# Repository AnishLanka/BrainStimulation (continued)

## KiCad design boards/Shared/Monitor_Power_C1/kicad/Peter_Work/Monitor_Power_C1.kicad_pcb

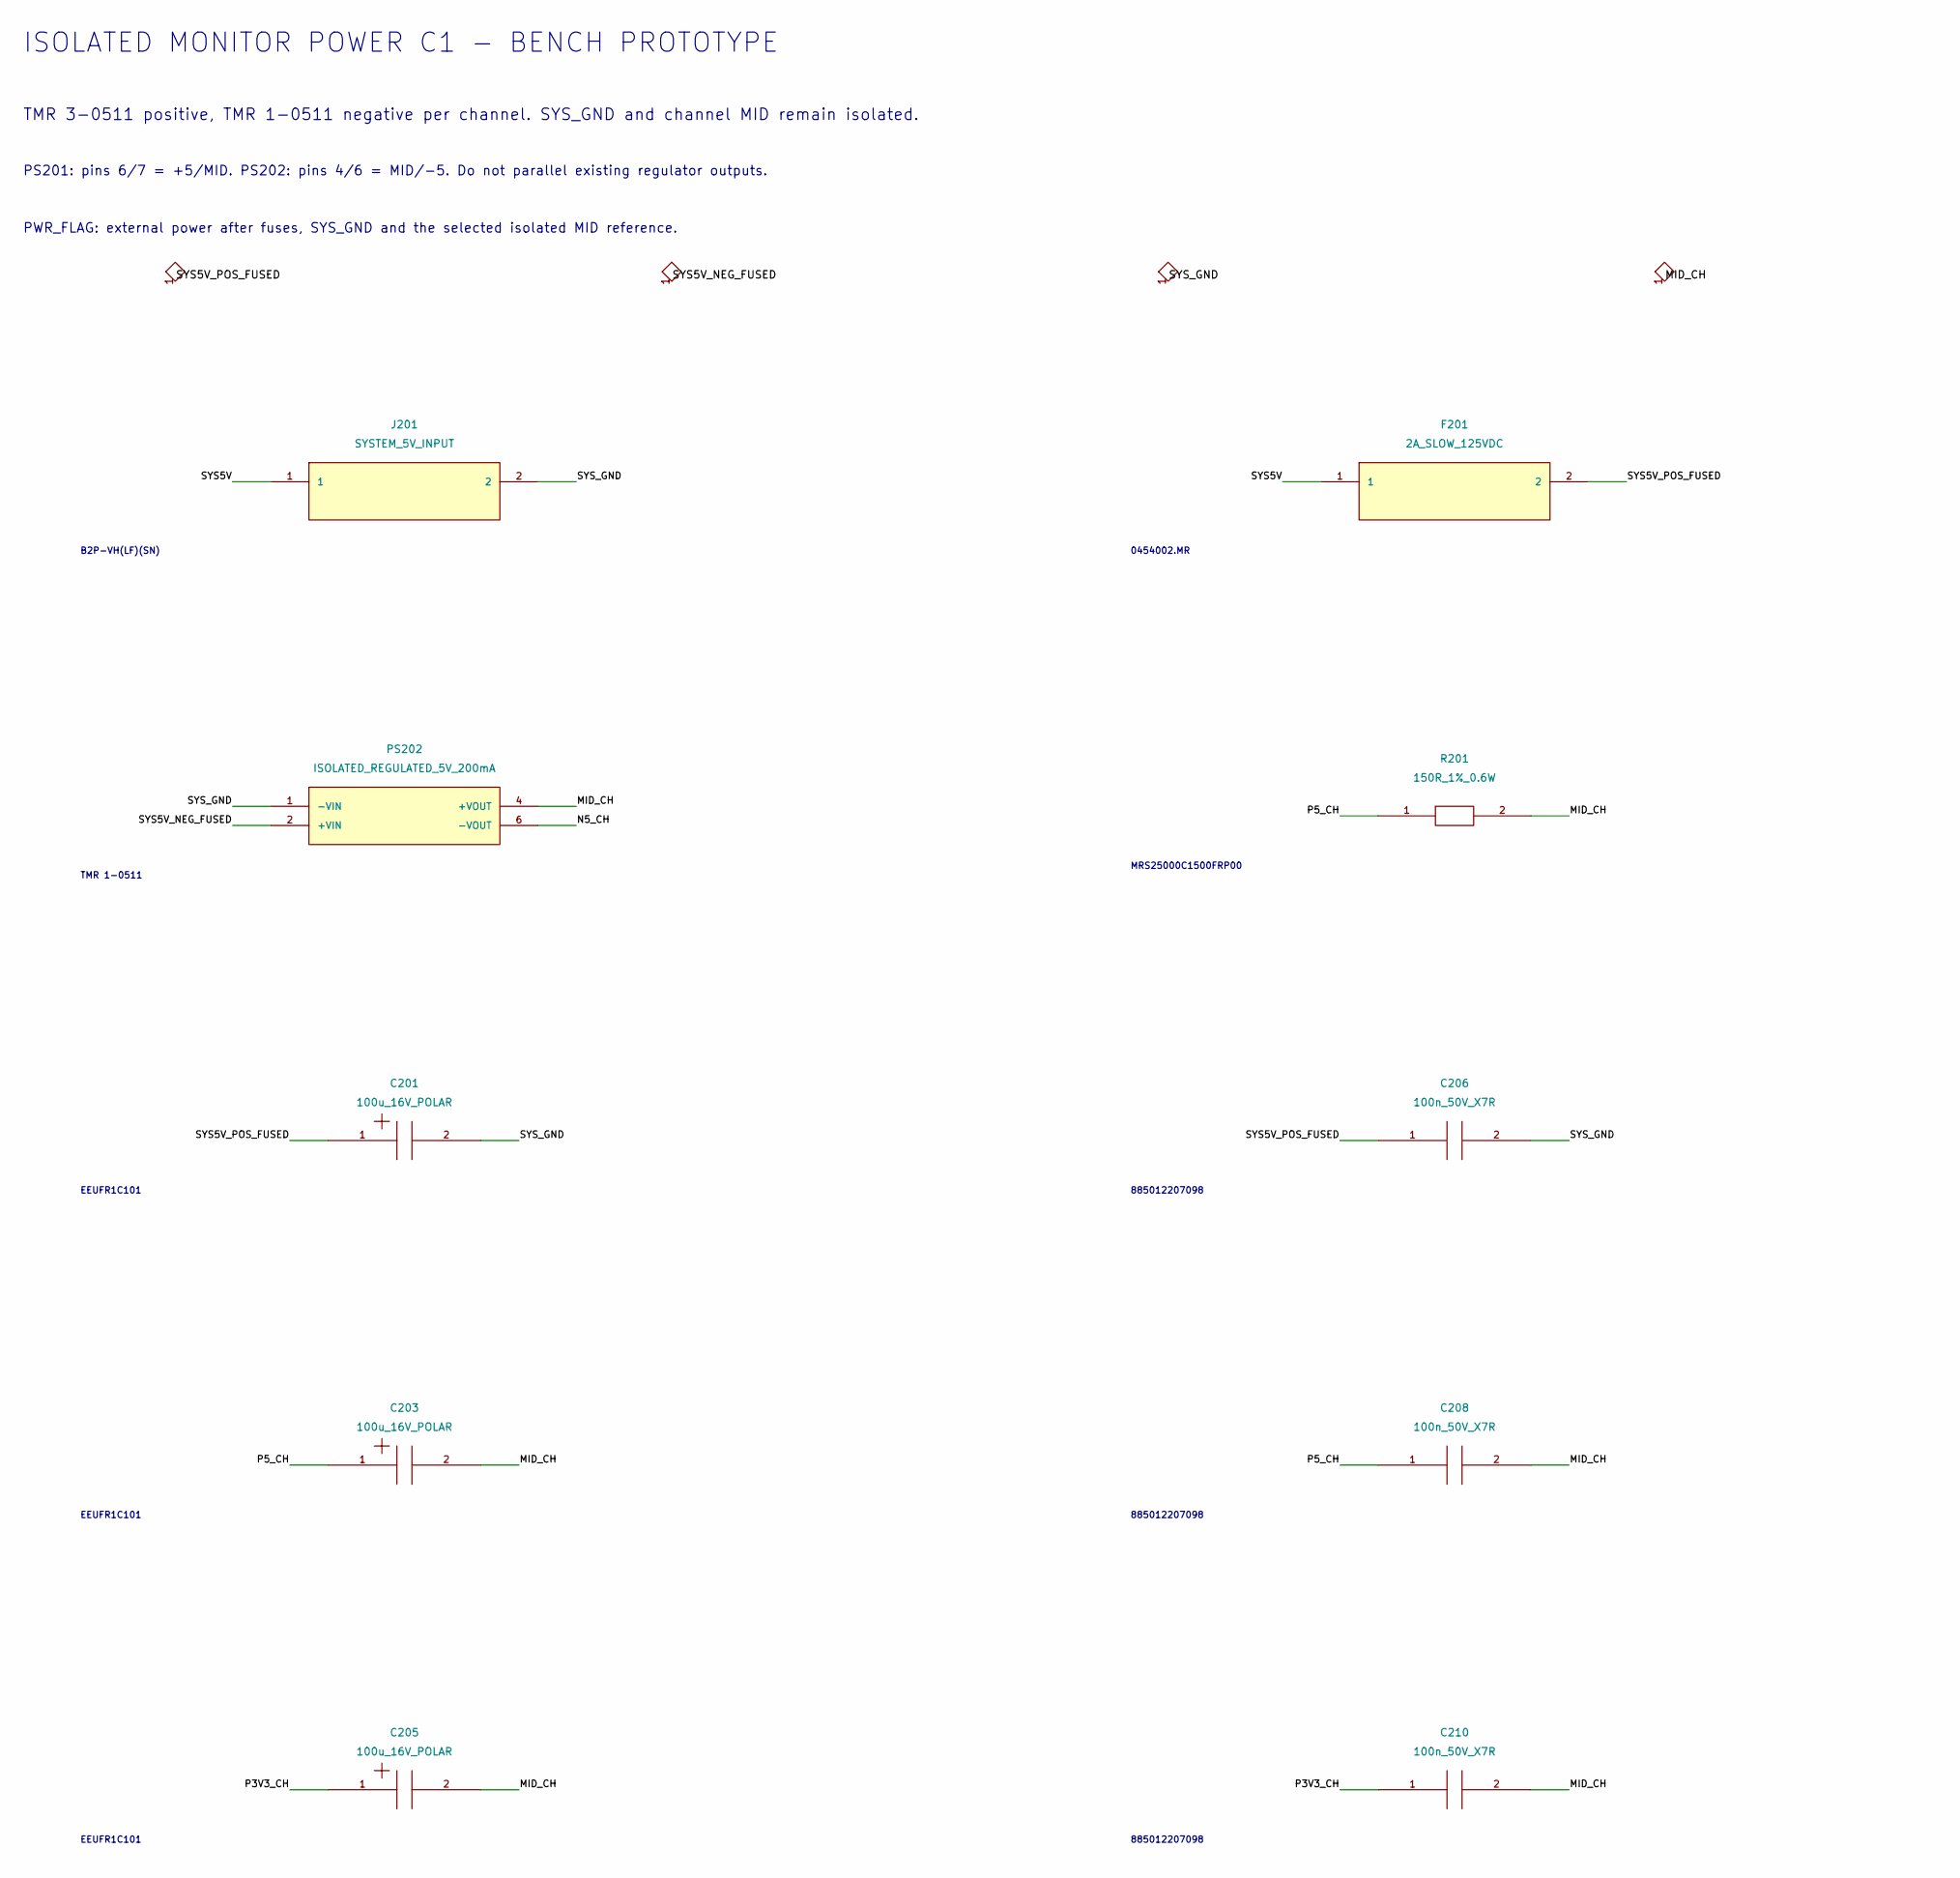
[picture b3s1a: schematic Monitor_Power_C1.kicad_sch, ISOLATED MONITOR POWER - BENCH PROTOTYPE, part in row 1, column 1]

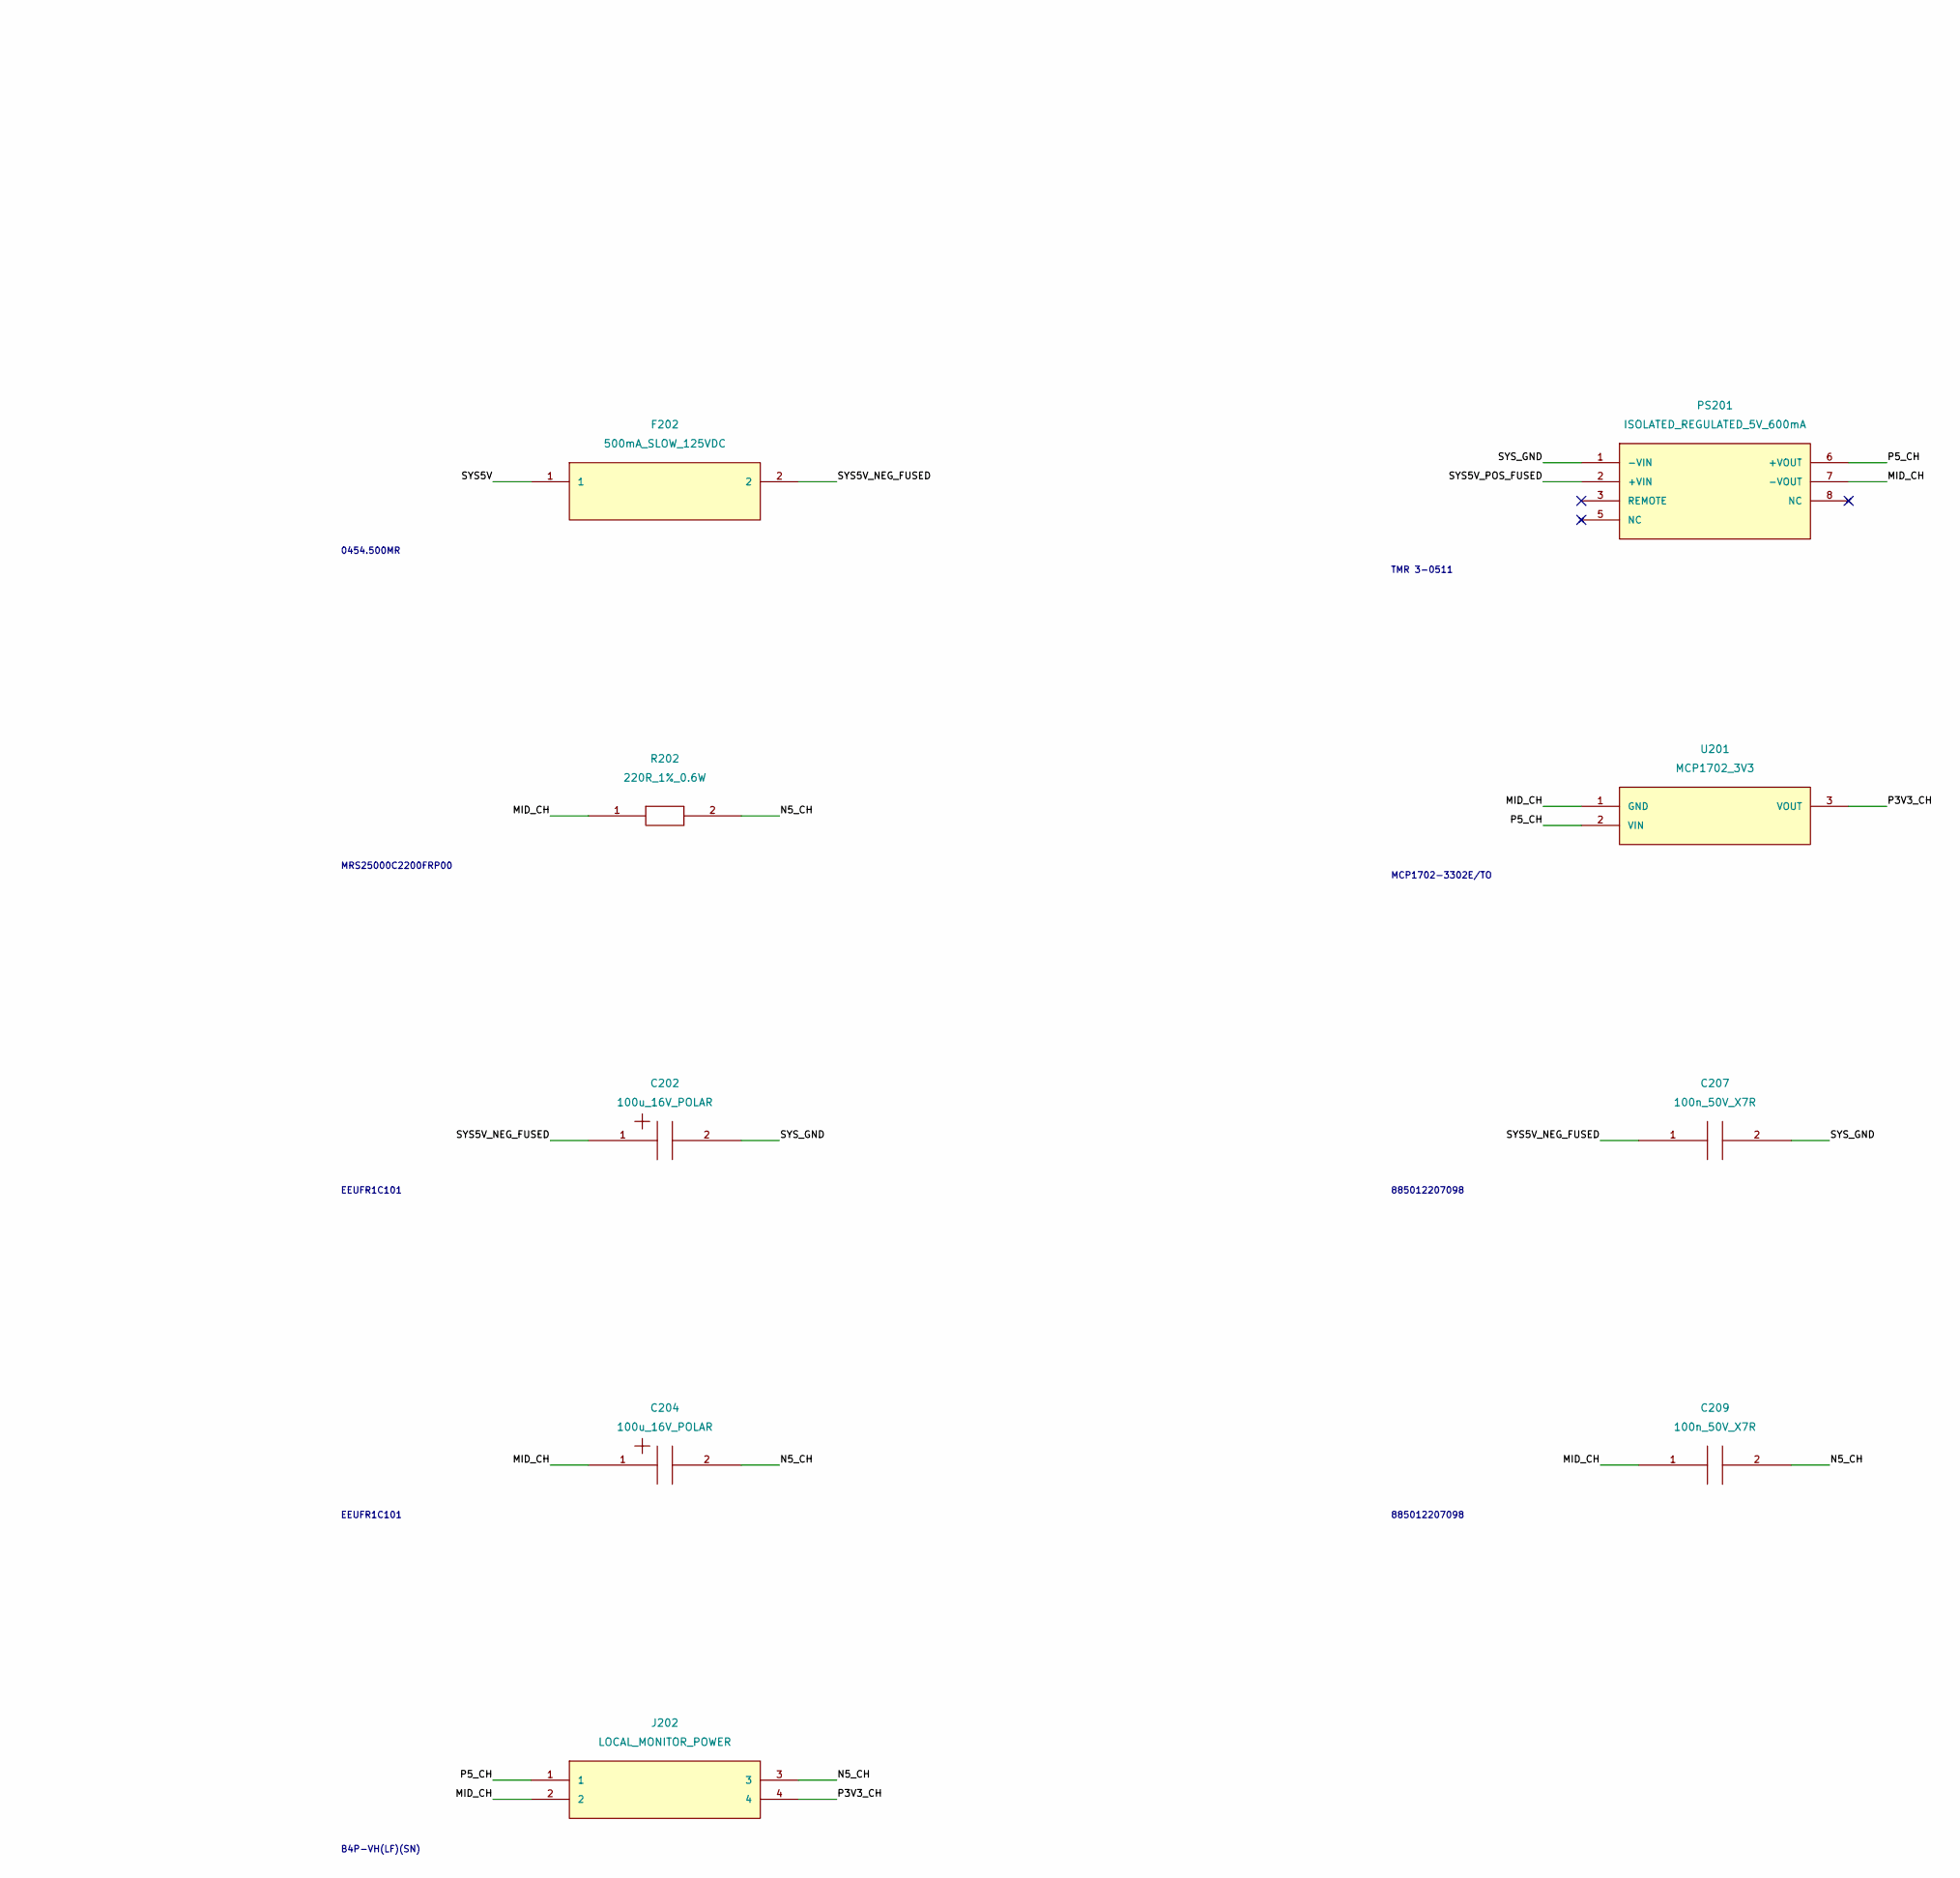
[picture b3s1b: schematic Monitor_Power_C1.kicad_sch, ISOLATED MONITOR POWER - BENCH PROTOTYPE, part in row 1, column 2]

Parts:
C201, C202, C203, C204, C205: 100u_16V_POLAR; Capacitor_THT_CP_Radial_D5.0mm_P2.00mm; MPN EEUFR1C101
C206, C207, C208, C209, C210: 100n_50V_X7R; Capacitor_SMD_C_0805_2012Metric; MPN 885012207098
F201: 2A_SLOW_125VDC; Fuse_Fuse_Littelfuse-NANO2-451_453; MPN 0454002.MR
F202: 500mA_SLOW_125VDC; Fuse_Fuse_Littelfuse-NANO2-451_453; MPN 0454.500MR
J201: SYSTEM_5V_INPUT; Connector_JST_JST_VH_B2P-VH_1x02_P3.96mm_Vertical; MPN B2P-VH(LF)(SN)
J202: LOCAL_MONITOR_POWER; Connector_JST_JST_VH_B4P-VH_1x04_P3.96mm_Vertical; MPN B4P-VH(LF)(SN)
PS201: ISOLATED_REGULATED_5V_600mA; ProtectionLocal_TRACO_TMR3_SIP8_Single; MPN TMR 3-0511
PS202: ISOLATED_REGULATED_5V_200mA; Converter_DCDC_Converter_DCDC_TRACO_TMR-1-xxxx_Single_THT; MPN TMR 1-0511
R201: 150R_1%_0.6W; Resistor_THT_R_Axial_DIN0207_L6.3mm_D2.5mm_P10.16mm_Horizon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; MPN MRS25000C1500FRP00
R202: 220R_1%_0.6W; Resistor_THT_R_Axial_DIN0207_L6.3mm_D2.5mm_P10.16mm_Horizon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; MPN MRS25000C2200FRP00
U201: MCP1702_3V3; Package_TO_SOT_THT_TO-92_Inline_Wide; MPN MCP1702-3302E/TO

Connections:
/MID_CH: C203.2, C204.1, C205.2, C208.2, C209.1, C210.2, J202.2, PS201.7 (-VOUT), PS202.4 (+VOUT), R201.2, R202.1, U201.1 (GND)
/N5_CH: C204.2, C209.2, J202.3, PS202.6 (-VOUT), R202.2
/P3V3_CH: C205.1, C210.1, J202.4, U201.3 (VOUT)
/P5_CH: C203.1, C208.1, J202.1, PS201.6 (+VOUT), R201.1, U201.2 (VIN)
/SYS5V: F201.1, F202.1, J201.1
/SYS5V_NEG_FUSED: C202.1, C207.1, F202.2, PS202.2 (+VIN)
/SYS5V_POS_FUSED: C201.1, C206.1, F201.2, PS201.2 (+VIN)
/SYS_GND: C201.2, C202.2, C206.2, C207.2, J201.2, PS201.1 (-VIN), PS202.1 (-VIN)

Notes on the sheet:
ISOLATED MONITOR POWER C1 - BENCH PROTOTYPE
TMR 3-0511 positive, TMR 1-0511 negative per channel. SYS_GND and channel MID remain isolated.
PS201: pins 6/7 = +5/MID. PS202: pins 4/6 = MID/-5. Do not parallel existing regulator outputs.
PWR_FLAG: external power after fuses, SYS_GND and the selected isolated MID reference.
B2P-VH(LF)(SN)
0454002.MR
0454.500MR
TMR 3-0511
TMR 1-0511
MRS25000C1500FRP00
MRS25000C2200FRP00
MCP1702-3302E/TO
EEUFR1C101
885012207098
B4P-VH(LF)(SN)

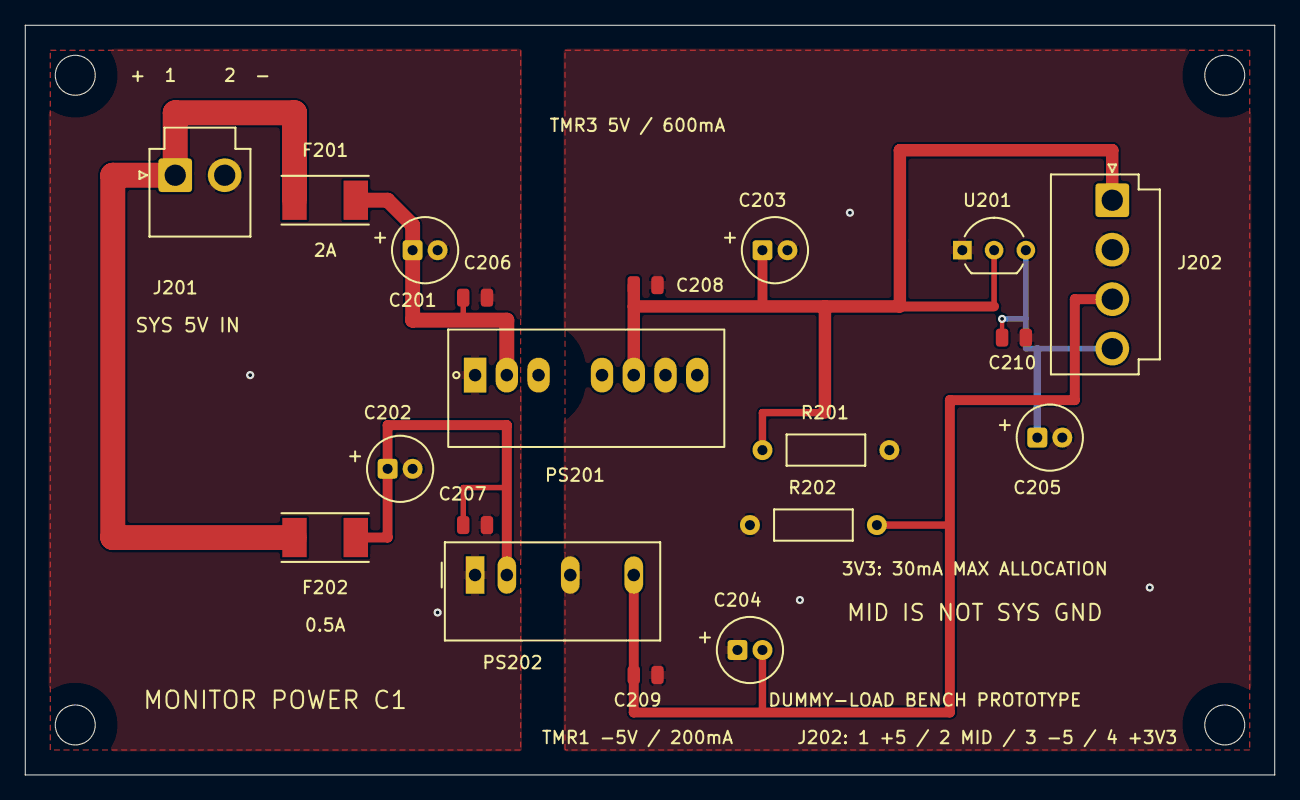
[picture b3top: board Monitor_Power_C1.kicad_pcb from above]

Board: 2 copper layers, 100.0 x 60.0 mm, 23 parts (0 on the bottom side), 8 nets.

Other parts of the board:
H1, H2, H3, H4: M3_NPTH

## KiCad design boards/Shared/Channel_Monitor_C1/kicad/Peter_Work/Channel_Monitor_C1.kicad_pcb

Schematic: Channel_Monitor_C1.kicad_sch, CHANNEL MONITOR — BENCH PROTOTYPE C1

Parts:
C1, C2, C3, C4, C5, C6, C7, C8, C9, C10, C14, C15, C16, C17, C18, C19: 100n; C_0805_2012Metric; MPN 885012207098
C11, C12: 1u; C_0805_2012Metric; MPN 885012207078
C13: 22u 25V X5R; C_0805_2012Metric; MPN C2012X5R1E226M125AC
C101, C102, C104: 100n50V; C_0805_2012Metric; MPN 885012207098
C103: 1u25V; C_0805_2012Metric; MPN 885382207003
D1: BAV199; SOT-23; MPN BAV199,215
D101: SMAJ12A_COIL_CLAMP; D_SMA; MPN SMAJ12A-E3/61
J1: ISOLATED_LOCAL_POWER; PinHeader_1x04_P2.54mm_Vertical; MPN TSW-104-07-G-S
J2: HOWLAND_OUTPUT_INPUT; PinHeader_1x02_P2.54mm_Vertical; MPN TSW-102-07-G-S
J3: ISOLATED_CONTROL; PinHeader_1x06_P2.54mm_Vertical; MPN TSW-106-07-G-S
J4: HOWLAND_ENABLE; PinHeader_1x02_P2.54mm_Vertical; MPN TSW-102-07-G-S
J5: SIMULTANEOUS_ADC_MODULE; PinHeader_1x07_P2.54mm_Vertical; MPN TSW-107-07-G-S
J6: FAULT_STATUS; PinHeader_1x03_P2.54mm_Vertical; MPN TSW-103-07-G-S
J7: HV_RAIL_MONITOR; PinHeader_1x03_P2.54mm_Vertical; MPN TSW-103-07-G-S
J8: COMMAND_MONITOR; PinHeader_1x02_P2.54mm_Vertical; MPN TSW-102-07-G-S
J101: EXTERNAL_DUMMY_LOAD; PinHeader_1x02_P2.54mm_Vertical; MPN TSW-102-07-G-S
K101: DPST_NO_5V; Pickering104_Package4_6Pin_P5.08; MPN 104-2-A-5/2
Q101: AO3400A; SOT-23; MPN AO3400A
R1: 100R 0.1%; R_1206_3216Metric; MPN TNPW1206100RBEEA
R2, R3: 20k; R_0805_2012Metric; MPN TNPW080520K0BEEA
R4, R6, R20, R21, R22, R23, R24, R26, R30, R32, R34, R35, R54, R56, R58, R60, R65, R67, R68, R69, R73, R75, R76, R77, R78, R102, R103: 10k; R_0805_2012Metric; MPN TNPW080510K0BEEA
R5, R7: 32.4k; R_0805_2012Metric; MPN TNPW080532K4BEEA
R8, R9, R11, R12, R43, R44, R45, R46, R48, R49, R50, R51, R61, R62, R63, R64: 499k; R_0805_2012Metric; MPN TNPW0805499KBEEA
R10, R13, R47, R52, R79: 49.9k; R_0805_2012Metric; MPN TNPW080549K9BEEA
R14, R16: 5.11k; R_0805_2012Metric; MPN TNPW08055K11BEEA
R15: 93.1k; R_0805_2012Metric; MPN TNPW080593K1BEEA
R17, R19: 15.6k; R_0805_2012Metric; MPN TNPW080515K6BEEA
R18: 71.5k; R_0805_2012Metric; MPN TNPW080571K5BEEA
R25, R37, R39: 1k; R_0805_2012Metric; MPN TNPW08051K00BEEA
R27, R71: 100k; R_0805_2012Metric; MPN TNPW0805100KBEEA
R28: 200k; R_0805_2012Metric; MPN TNPW0805200KBEEA
R29: 24.9k; R_0805_2012Metric; MPN TNPW080524K9BEEA
R31, R57: 35.7k; R_0805_2012Metric; MPN TNPW080535K7BEEA
R33: 88.7k; R_0805_2012Metric; MPN TNPW080588K7BEEA
R36: 22.1k 1% 0.75W; R_2010_5025Metric; MPN CRCW201022K1FKEF
R38, R40: 249R; R_0805_2012Metric; MPN TNPW0805249RBEEA
R41, R42: 470R 1% 0.25W; R_1206_3216Metric; MPN CRCW1206470RFKEA
R53: 4.42k; R_0805_2012Metric; MPN TNPW08054K42BEEA
R55: 3.24k; R_0805_2012Metric; MPN TNPW08053K24BEEA
R59: 25.5k; R_0805_2012Metric; MPN TNPW080525K5BEEA
R66: 10.8k; R_0805_2012Metric; MPN TNPW080510K8BEEA
R70: 300k; R_0805_2012Metric; MPN TNPW0805300KBEEA
R72: 16.9k; R_0805_2012Metric; MPN TNPW080516K9BEEA
R74: 16.5k; R_0805_2012Metric; MPN TNPW080516K5BEEA
R101: 100R; R_0805_2012Metric; MPN TNPW0805100RBEEA
TP1: I_MON; TestPoint_Pad_D1.0mm; MPN PCB_FEATURE_NO_COMPONENT
TP2: V_MON; TestPoint_Pad_D1.0mm; MPN PCB_FEATURE_NO_COMPONENT
TP3: FAULT_N; TestPoint_Pad_D1.0mm; MPN PCB_FEATURE_NO_COMPONENT
TP4: BIAS_2V048; TestPoint_Pad_D1.0mm; MPN PCB_FEATURE_NO_COMPONENT
U1, U2: OPA2192; SOIC-8_3.9x4.9mm_P1.27mm; MPN OPA2192ID
U3: REF5040A; SOIC-8_3.9x4.9mm_P1.27mm; MPN REF5040AID
U4, U11: TLV1704; TSSOP-14_4.4x5mm_P0.65mm; MPN TLV1704IPWR
U5: SN74LVC1G74; VSSOP-8_2.3x2mm_P0.5mm; MPN SN74LVC1G74DCUR
U6: TPS3808G33; SOT-23-6; MPN TPS3808G33DBVR
U7: TPS3808G50; SOT-23-6; MPN TPS3808G50DBVR
U8, U12, U13: TLV1702; VSSOP-8_3x3mm_P0.65mm; MPN TLV1702IDGKR
U9, U14, U15, U101: TPS3808G01; SOT-23-6; MPN TPS3808G01DBVR
U10: TPS3431; Texas_DRB0008A; MPN TPS3431SDRBR
U16: SN74LVC2G17; SOT-23-6; MPN SN74LVC2G17DBVR
U102: SN74LVC1G08; SOT-23-5; MPN SN74LVC1G08DBVR
U103: SN74LVC1G17; SOT-23-5; MPN SN74LVC1G17DBVR

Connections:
/AMP_ARMED: R25.1, U102.4 (Y)
/ARMED: R35.1, R101.1, U5.5 (Q), U101.3 (MR_N), U102.1 (A)
/ARM_EDGE: J3.3, R21.1, U5.1 (CLK)
/BALN_MID: R63.2, R64.1
/BALP_MID: R61.2, R62.1
/BIAS_2V048: R5.1, R10.1, R47.1, R52.1, R65.1, R71.1, TP4.1 (1_1), U1.6 (INB-), U1.7 (OUTB)
/BIAS_DIV: R2.2, R3.1, U1.5 (INB+)
/CMD_FROM_SIGNAL: J8.1, R70.1
/CMD_HIGH: R74.2, R75.1, U13.5 (IN2+)
/CMD_LOW: R72.2, R73.1, U13.2 (IN1-)
/CMD_SENSE: R70.2, R71.2, U13.3 (IN1+), U13.6 (IN2-)
/COIL_GATE: Q101.1 (G), R101.2, R102.1
/COIL_LOW: D101.1 (K), K101.4 (COIL-), Q101.3 (D)
/CWD: R24.2, U10.2 (CWD)
/EXTERNAL_N: J101.2, K101.5 (CONTACT_B_OUT)
/EXTERNAL_P: J101.1, K101.6 (CONTACT_A_OUT)
/FAULT_CLEAR_N: J6.1, U5.6 (~CLR), U16.6 (1Y)
/FAULT_COND_N: R78.2, U15.1 (~RESET), U16.1 (1A)
/FAULT_N: J3.5, J5.7, R20.2, TP3.1 (1_1), U4.1 (OUT2), U4.2 (OUT1), U4.13 (OUT4), U4.14 (OUT3), U6.1 (~RESET), U7.1 (~RESET), U8.1 (OUT1), U8.7 (OUT2), U9.1 (~RESET), U10.7 (~WDO), U10.8 (ENOUT), U11.1 (OUT2), U11.2 (OUT1), U11.13 (OUT4), U11.14 (OUT3), U12.1 (OUT1), U12.7 (OUT2), U15.3 (~MR)
/HEARTBEAT: J3.4, R23.1, U10.6 (WDI)
/HVN_DIV1: R48.2, R49.1
/HVN_DIV2: R49.2, R50.1
/HVN_DIV3: R50.2, R51.1
/HVN_HIGH: R59.2, R60.1, U11.11 (IN4+)
/HVN_LOW: R57.2, R58.1, U11.8 (IN3-)
/HVN_SENSE: R51.2, R52.2, U11.9 (IN3+), U11.10 (IN4-)
/HVP_DIV1: R43.2, R44.1
/HVP_DIV2: R44.2, R45.1
/HVP_DIV3: R45.2, R46.1
/HVP_HIGH: R55.2, R56.1, U11.7 (IN2+)
/HVP_LOW: R53.2, R54.1, U11.4 (IN1-)
/HVP_SENSE: R46.2, R47.2, U11.5 (IN1+), U11.6 (IN2-)
/HV_BOTTOM: J7.3, R48.1, R63.1
/HV_TOP: J7.1, R43.1, R61.1
/INHIBITED: J3.6, U5.3 (~Q)
/INTERNAL_N: K101.2 (CONTACT_B_IN), R1.1, R36.1
/INTERNAL_P: J2.1, K101.1 (CONTACT_A_IN), R8.1
/I_HIGH: R15.2, R16.1, U4.7 (IN2+)
/I_LOW: R14.2, R15.1, U4.4 (IN1-)
/I_MINUS: R6.2, R7.2, U2.2 (INA-)
/I_MON: J5.2, R7.1, TP1.1 (1_1), U2.1 (OUTA), U4.5 (IN1+), U4.6 (IN2-)
/I_PLUS: R4.2, R5.2, U2.3 (INA+)
/MID_BAL_HIGH: R68.2, R69.1, U12.5 (IN2+)
/MID_BAL_LOW: R66.2, R67.1, U12.2 (IN1-)
/MID_BAL_SENSE: R62.2, R64.2, R65.2, U12.3 (IN1+), U12.6 (IN2-)
/MID_CH: C1.2, C2.2, C3.2, C4.2, C5.2, C6.2, C7.2, C8.2, C9.2, C10.2, C11.2, C12.2, C13.2, C14.2, C15.2, C16.2, C17.2, C18.2, C19.2, C101.2, C102.2, C103.2, C104.2, D101.2 (A), J1.2, J2.2, J3.1, J4.2, J5.1, J6.2, J7.2, J8.2, Q101.2 (S), R1.2, R3.2, R6.1, R14.1, R17.1, R21.2, R22.2, R23.2, R26.2, R30.2, R32.2, R34.2, R35.2, R38.2, R40.1, R41.2, R42.1, R54.2, R56.2, R58.2, R60.2, R67.2, R69.2, R73.2, R75.2, R102.2, U2.4 (V-), U3.4 (GND), U4.12 (V-), U5.4 (GND), U6.2 (GND), U7.2 (GND), U8.4 (V-), U9.2 (GND), U10.4 (GND), U10.9 (EP), U11.12 (V-), U12.4 (V-), U13.4 (V-), U14.2 (GND), U15.2 (GND), U16.2 (GND), U101.2 (GND), U102.3 (GND), U103.3 (GND)
/N5_CH: C2.1, J1.3, R28.2, R39.2, R42.2, U1.4 (V-)
/N5_HIGH: R29.2, R30.1, U8.3 (IN1+)
/N5_LOW: R31.2, R32.1, U8.6 (IN2-)
/N5_SENSE: R27.2, R28.1, U8.2 (IN1-), U8.5 (IN2+)
/N_CLAMP: D1.1 (A1), R39.1, R40.2
/OPA_ENABLE: J4.1, R25.2, R26.1
/P3V3_CH: C5.1, C6.1, C7.1, C9.1, C10.1, C17.1, C18.1, C19.1, C101.1, C102.1, C104.1, J1.4, J5.6, J6.3, R20.1, R24.1, R76.1, R77.1, R78.1, R79.1, R103.1, U5.7 (~PRE), U5.8 (VCC), U6.3 (~MR), U6.5 (SENSE), U6.6 (VDD), U7.3 (~MR), U7.6 (VDD), U9.3 (~MR), U9.6 (VDD), U10.1 (VDD), U10.5 (SET1), U14.5 (SENSE), U14.6 (VDD), U15.5 (SENSE), U15.6 (VDD), U16.5 (VCC), U101.5 (SENSE), U101.6 (VDD), U102.5 (VCC), U103.5 (VCC)
/P5_CH: C1.1, C3.1, C4.1, C8.1, C11.1, C14.1, C15.1, C16.1, C103.1, J1.1, J5.5, K101.3 (COIL+), R37.1, R41.1, U1.8 (V+), U2.8 (V+), U3.2 (VIN), U4.3 (V+), U7.5 (SENSE), U8.8 (V+), U11.3 (V+), U12.8 (V+), U13.8 (V+)
/P_CLAMP: D1.2 (K2), R37.2, R38.1
/REF_4V096: C13.1, J5.4, R2.1, R16.2, R19.2, R27.1, R29.1, R31.1, R33.1, R53.1, R55.1, R57.1, R59.1, R66.1, R68.1, R72.1, R74.1, U3.6 (VOUT)
/REF_NR: C12.1, U3.5 (TRIM/NR)
/REF_SENSE: R33.2, R34.1, U9.5 (SENSE)
/RELAY_DELAY_N: R103.2, U101.1 (RESET_N), U103.2 (A)
/RELAY_SETTLED: U102.2 (B), U103.4 (Y)
/RETURN_BUF: R4.1, R11.1, U1.1 (OUTA), U1.2 (INA-)
/RETURN_PROTECTED: D1.3 (K1_A2), R36.2, U1.3 (INA+)
/RUN_REQUEST: J3.2, R22.1, U10.3 (EN)
/V_HIGH: R18.2, R19.1, U4.11 (IN4+)
/V_LOW: R17.2, R18.1, U4.8 (IN3-)
/V_MINUS: R12.2, R13.2, U2.6 (INB-)
/V_MON: J5.3, R13.1, TP2.1 (1_1), U2.7 (OUTB), U4.9 (IN3+), U4.10 (IN4-)
/V_NEG_MID: R11.2, R12.1
/V_PLUS: R9.2, R10.2, U2.5 (INB+)
/V_POS_MID: R8.2, R9.1
/ZERO_ARM_OK: U5.2 (D), U16.4 (2Y)
/ZERO_CT: R79.2, U14.4 (CT)
/ZERO_QUAL_N: R77.2, U14.1 (~RESET), U16.3 (2A)
/ZERO_RAW: R76.2, U13.1 (OUT1), U13.7 (OUT2), U14.3 (~MR)

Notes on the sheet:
CHANNEL MONITOR C1 — BENCH PROTOTYPE
Single isolated domain. 0.5 Hz–40 kHz target; nominal +/-40 V Howland supplies. Monitor supply uses separately regulated +/-5 V and 3.3 V.
Howland remains unchanged. This monitor senses the external branch and opens a relay. J4 enable is optional; no instantaneous port limit is claimed.
J1 external supply annotations:
OPA2192ID
REF5040AID
TLV1704IPWR
SN74LVC1G74DCUR
TPS3808G33DBVR
TPS3808G50DBVR
TLV1702IDGKR
TPS3808G01DBVR
TPS3431SDRBR
TNPW1206100RBEEA
TNPW080520K0BEEA
TNPW080510K0BEEA
TNPW080532K4BEEA
TNPW0805499KBEEA
TNPW080549K9BEEA
TNPW08055K11BEEA
TNPW080593K1BEEA
TNPW080515K6BEEA
TNPW080571K5BEEA
TNPW08051K00BEEA
TNPW0805100KBEEA
TNPW0805200KBEEA
TNPW080524K9BEEA
TNPW080535K7BEEA
TNPW080588K7BEEA
885012207098
TSW-104-07-G-S
TSW-102-07-G-S
TSW-106-07-G-S
TSW-107-07-G-S
TSW-103-07-G-S
PCB_FEATURE_NO_COMPONENT
CRCW201022K1FKEF
BAV199,215
TNPW0805249RBEEA
CRCW1206470RFKEA

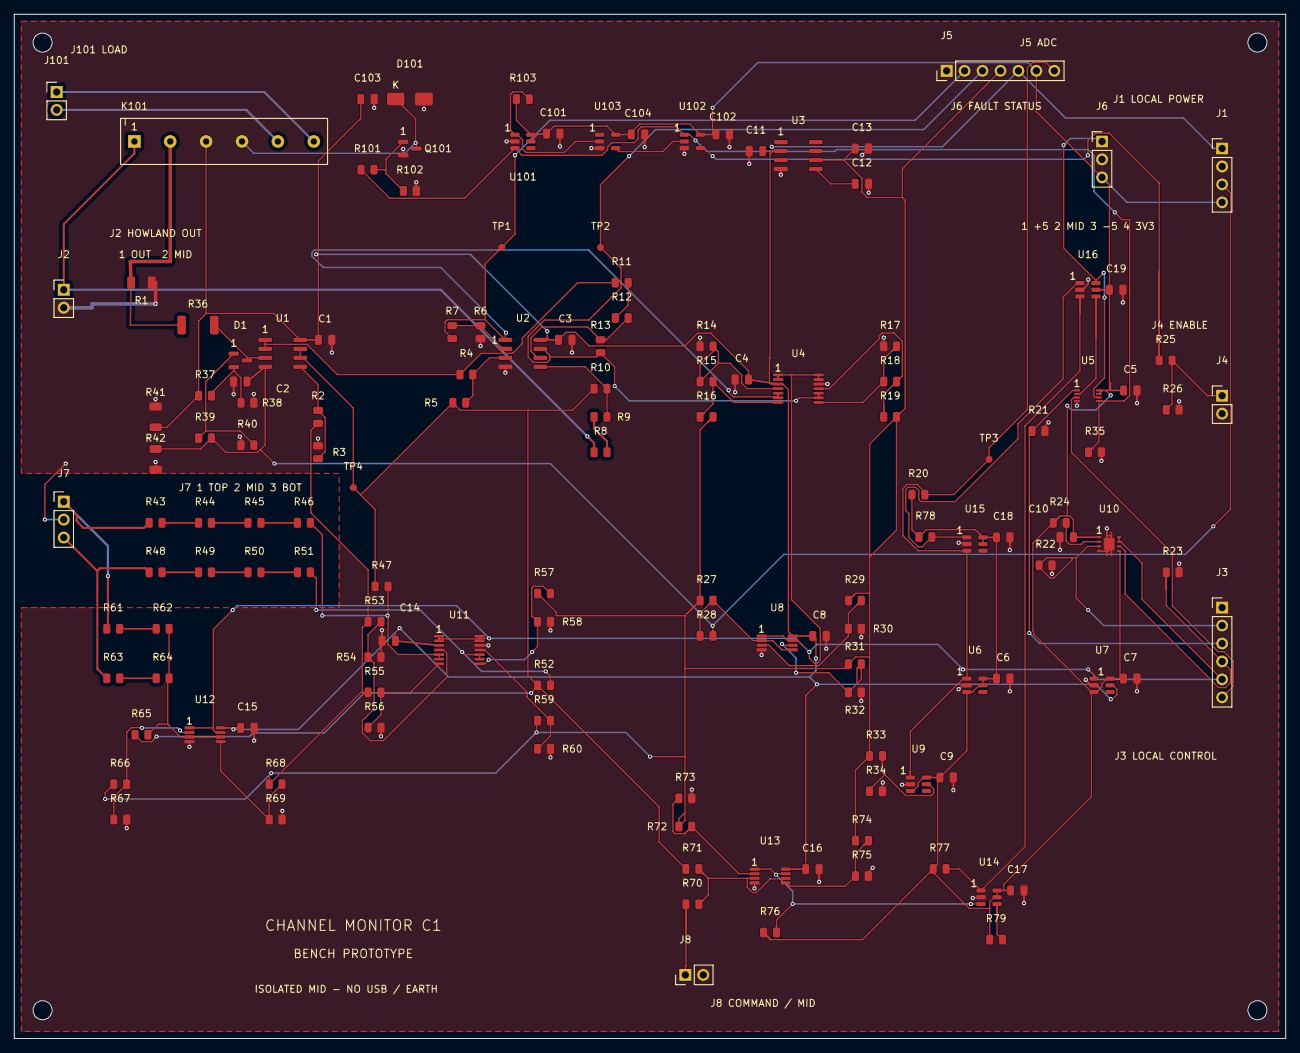
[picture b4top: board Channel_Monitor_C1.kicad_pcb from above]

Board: 2 copper layers, 180.0 x 145.0 mm, 145 parts (0 on the bottom side), 74 nets.

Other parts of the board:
H1, H2, H3, H4: M2.5 support; MountingHole_2.7mm_M2.5

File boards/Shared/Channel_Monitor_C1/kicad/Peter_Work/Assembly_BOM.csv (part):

Reference,Value,MPN,Manufacturer,Footprint,Population,Notes,Primary_sources
U1,OPA2192,OPA2192ID,,Package_SO:SOIC-8_3.9x4.9mm_P1.27mm,Fit,"Dual regulated +/-5 V supply. A buffers protected load return; B buffers half-reference. Input protection is specified for bounded +/-80 V fault injection, not arbitrary surges.",
U2,OPA2192,OPA2192ID,,Package_SO:SOIC-8_3.9x4.9mm_P1.27mm,Fit,Single 5 V supply. A current difference gain3.24; B voltage difference gain1/20.,
U3,REF5040A,REF5040AID,,Package_SO:SOIC-8_3.9x4.9mm_P1.27mm,Fit,"Standard grade0.1%,8ppm/C. Pins1/8DNC;3TEMP unused;7NC.",
U4,TLV1704,TLV1704IPWR,,Package_SO:TSSOP-14_4.4x5mm_P0.65mm,Fit,All four open-collector outputs wired together. Each comparator is high-impedance in its acceptable window.,
U5,SN74LVC1G74,SN74LVC1G74DCUR,,Package_SO:VSSOP-8_2.3x2mm_P0.5mm,Fit,"Pin 5 Q, pin 3 inverted Q. D samples qualified near-zero command at rising ARM_EDGE only. Conditioned asynchronous clear is FAULT_CLEAR_N. Hold ARM low through faults; allow at least 1 us after clear recovery before a new rising edge. No automatic rearm.",
U6,TPS3808G33,TPS3808G33DBVR,,Package_TO_SOT_SMD:SOT-23-6,Fit,3.3V supervisor3.07Vnom; CTopen20msreset release.,
U7,TPS3808G50,TPS3808G50DBVR,,Package_TO_SOT_SMD:SOT-23-6,Fit,Monitors+5V at4.65Vnom; powered3.3V. CTopen20ms.,
U8,TLV1702,TLV1702IDGKR,,Package_SO:VSSOP-8_3x3mm_P0.65mm,Fit,Negative rail window approximate-5.503V to-4.671V. Precision tolerances/offset must be included in regulator choice.,
U9,TPS3808G01,TPS3808G01DBVR,,Package_TO_SOT_SMD:SOT-23-6,Fit,Reference undervoltage nominal3.997V; CTopen20ms. Does not detect reference overvoltage.,
U10,TPS3431,TPS3431SDRBR,,Package_DFN_QFN:Texas_DRB0008A,Fit,"WDO and ENOUT wired together. SET1high,CWD10ktoVDD ->170/200/230ms. EPpin9 is schematic convention; verify package pad geometry.",
R1,100R 0.1%,TNPW1206100RBEEA,Vishay,Resistor_SMD:R_1206_3216Metric,Fit,"Manufacturer resistance code uses R/K/M decimal notation; B=0.1%, E=25 ppm/K, EA=tape packaging. Electrical value and footprint unchanged. TNPW0805 0.1%/25 ppm range includes 499 kohm (up to 1 Mohm).",https://www.vishay.com/docs/28758/tnpw_e3.pdf
R2,20k,TNPW080520K0BEEA,Vishay,Resistor_SMD:R_0805_2012Metric,Fit,"Manufacturer resistance code uses R/K/M decimal notation; B=0.1%, E=25 ppm/K, EA=tape packaging. Electrical value and footprint unchanged. TNPW0805 0.1%/25 ppm range includes 499 kohm (up to 1 Mohm).",https://www.vishay.com/docs/28758/tnpw_e3.pdf
R3,20k,TNPW080520K0BEEA,Vishay,Resistor_SMD:R_0805_2012Metric,Fit,"Manufacturer resistance code uses R/K/M decimal notation; B=0.1%, E=25 ppm/K, EA=tape packaging. Electrical value and footprint unchanged. TNPW0805 0.1%/25 ppm range includes 499 kohm (up to 1 Mohm).",https://www.vishay.com/docs/28758/tnpw_e3.pdf
R4,10k,TNPW080510K0BEEA,Vishay,Resistor_SMD:R_0805_2012Metric,Fit,"Manufacturer resistance code uses R/K/M decimal notation; B=0.1%, E=25 ppm/K, EA=tape packaging. Electrical value and footprint unchanged. TNPW0805 0.1%/25 ppm range includes 499 kohm (up to 1 Mohm).",https://www.vishay.com/docs/28758/tnpw_e3.pdf
R5,32.4k,TNPW080532K4BEEA,Vishay,Resistor_SMD:R_0805_2012Metric,Fit,"Manufacturer resistance code uses R/K/M decimal notation; B=0.1%, E=25 ppm/K, EA=tape packaging. Electrical value and footprint unchanged. TNPW0805 0.1%/25 ppm range includes 499 kohm (up to 1 Mohm).",https://www.vishay.com/docs/28758/tnpw_e3.pdf
R6,10k,TNPW080510K0BEEA,Vishay,Resistor_SMD:R_0805_2012Metric,Fit,"Manufacturer resistance code uses R/K/M decimal notation; B=0.1%, E=25 ppm/K, EA=tape packaging. Electrical value and footprint unchanged. TNPW0805 0.1%/25 ppm range includes 499 kohm (up to 1 Mohm).",https://www.vishay.com/docs/28758/tnpw_e3.pdf
R7,32.4k,TNPW080532K4BEEA,Vishay,Resistor_SMD:R_0805_2012Metric,Fit,"Manufacturer resistance code uses R/K/M decimal notation; B=0.1%, E=25 ppm/K, EA=tape packaging. Electrical value and footprint unchanged. TNPW0805 0.1%/25 ppm range includes 499 kohm (up to 1 Mohm).",https://www.vishay.com/docs/28758/tnpw_e3.pdf
R8,499k,TNPW0805499KBEEA,Vishay,Resistor_SMD:R_0805_2012Metric,Fit,"Manufacturer resistance code uses R/K/M decimal notation; B=0.1%, E=25 ppm/K, EA=tape packaging. Electrical value and footprint unchanged. TNPW0805 0.1%/25 ppm range includes 499 kohm (up to 1 Mohm).",https://www.vishay.com/docs/28758/tnpw_e3.pdf
R9,499k,TNPW0805499KBEEA,Vishay,Resistor_SMD:R_0805_2012Metric,Fit,"Manufacturer resistance code uses R/K/M decimal notation; B=0.1%, E=25 ppm/K, EA=tape packaging. Electrical value and footprint unchanged. TNPW0805 0.1%/25 ppm range includes 499 kohm (up to 1 Mohm).",https://www.vishay.com/docs/28758/tnpw_e3.pdf
R10,49.9k,TNPW080549K9BEEA,Vishay,Resistor_SMD:R_0805_2012Metric,Fit,"Manufacturer resistance code uses R/K/M decimal notation; B=0.1%, E=25 ppm/K, EA=tape packaging. Electrical value and footprint unchanged. TNPW0805 0.1%/25 ppm range includes 499 kohm (up to 1 Mohm).",https://www.vishay.com/docs/28758/tnpw_e3.pdf
R11,499k,TNPW0805499KBEEA,Vishay,Resistor_SMD:R_0805_2012Metric,Fit,"Manufacturer resistance code uses R/K/M decimal notation; B=0.1%, E=25 ppm/K, EA=tape packaging. Electrical value and footprint unchanged. TNPW0805 0.1%/25 ppm range includes 499 kohm (up to 1 Mohm).",https://www.vishay.com/docs/28758/tnpw_e3.pdf
R12,499k,TNPW0805499KBEEA,Vishay,Resistor_SMD:R_0805_2012Metric,Fit,"Manufacturer resistance code uses R/K/M decimal notation; B=0.1%, E=25 ppm/K, EA=tape packaging. Electrical value and footprint unchanged. TNPW0805 0.1%/25 ppm range includes 499 kohm (up to 1 Mohm).",https://www.vishay.com/docs/28758/tnpw_e3.pdf
R13,49.9k,TNPW080549K9BEEA,Vishay,Resistor_SMD:R_0805_2012Metric,Fit,"Manufacturer resistance code uses R/K/M decimal notation; B=0.1%, E=25 ppm/K, EA=tape packaging. Electrical value and footprint unchanged. TNPW0805 0.1%/25 ppm range includes 499 kohm (up to 1 Mohm).",https://www.vishay.com/docs/28758/tnpw_e3.pdf
R14,5.11k,TNPW08055K11BEEA,Vishay,Resistor_SMD:R_0805_2012Metric,Fit,"Manufacturer resistance code uses R/K/M decimal notation; B=0.1%, E=25 ppm/K, EA=tape packaging. Electrical value and footprint unchanged. TNPW0805 0.1%/25 ppm range includes 499 kohm (up to 1 Mohm).",https://www.vishay.com/docs/28758/tnpw_e3.pdf
R15,93.1k,TNPW080593K1BEEA,Vishay,Resistor_SMD:R_0805_2012Metric,Fit,"Manufacturer resistance code uses R/K/M decimal notation; B=0.1%, E=25 ppm/K, EA=tape packaging. Electrical value and footprint unchanged. TNPW0805 0.1%/25 ppm range includes 499 kohm (up to 1 Mohm).",https://www.vishay.com/docs/28758/tnpw_e3.pdf
R16,5.11k,TNPW08055K11BEEA,Vishay,Resistor_SMD:R_0805_2012Metric,Fit,"Manufacturer resistance code uses R/K/M decimal notation; B=0.1%, E=25 ppm/K, EA=tape packaging. Electrical value and footprint unchanged. TNPW0805 0.1%/25 ppm range includes 499 kohm (up to 1 Mohm).",https://www.vishay.com/docs/28758/tnpw_e3.pdf
R17,15.6k,TNPW080515K6BEEA,Vishay,Resistor_SMD:R_0805_2012Metric,Fit,"Manufacturer resistance code uses R/K/M decimal notation; B=0.1%, E=25 ppm/K, EA=tape packaging. Electrical value and footprint unchanged. TNPW0805 0.1%/25 ppm range includes 499 kohm (up to 1 Mohm).",https://www.vishay.com/docs/28758/tnpw_e3.pdf
R18,71.5k,TNPW080571K5BEEA,Vishay,Resistor_SMD:R_0805_2012Metric,Fit,"Manufacturer resistance code uses R/K/M decimal notation; B=0.1%, E=25 ppm/K, EA=tape packaging. Electrical value and footprint unchanged. TNPW0805 0.1%/25 ppm range includes 499 kohm (up to 1 Mohm).",https://www.vishay.com/docs/28758/tnpw_e3.pdf
R19,15.6k,TNPW080515K6BEEA,Vishay,Resistor_SMD:R_0805_2012Metric,Fit,"Manufacturer resistance code uses R/K/M decimal notation; B=0.1%, E=25 ppm/K, EA=tape packaging. Electrical value and footprint unchanged. TNPW0805 0.1%/25 ppm range includes 499 kohm (up to 1 Mohm).",https://www.vishay.com/docs/28758/tnpw_e3.pdf
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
